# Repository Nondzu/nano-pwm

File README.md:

# nano-pwm
### PC fan controller based on arduino nano

_______________

##### This controller have 3 independent PWM channels with 25 kHz according to PC fan specification.

##### Serial port (9600bps) is use to communicate with  arduino nano. 

##### AT COMMAND:
* set PWM: <br />
`AT+PWM=$value` - set pwm value for all channels<br />
`AT+PWM=($channel, $value)` - set pwm $value for $channel<br />

* read RPM info: <br />
`AT?RPM` - get RPM values from all channels <br />

Each command must finish be new line character `\n`

example:<br />
`AT+PWM=50` - set all channel PWM to 50%<br />
`AT+PWM=(0,90)` - set channel 0 to 90% PWM. <br />
`AT+PWM=(2,50)` - set channel 2 to 50% PWM. <br />
`AT?RPM` - get rpm value from all channels<br />

-------
#### SCHEMATIC:
Schematic will be available soon. PWM and tachometer pins can by connecting directly to arduino. Additional items are not necessary (resistor or transistors).
here is connection info:<br /><br />
FAN PWM (OUTPUT):<br />
 PIN 9 - PWM output for channel 0<br />
 PIN 10 - PWM output for channel 1<br />
 PIN 3 - PWM output for channel 2<br />
<br />
FAN tachometer (INPUT):<br />
 PIN 4 - RPM CHANNEL 0<br />
 PIN 5 - RPM CHANNEL 1<br />
 PIN 6 - RPM CHANNEL 2<br />

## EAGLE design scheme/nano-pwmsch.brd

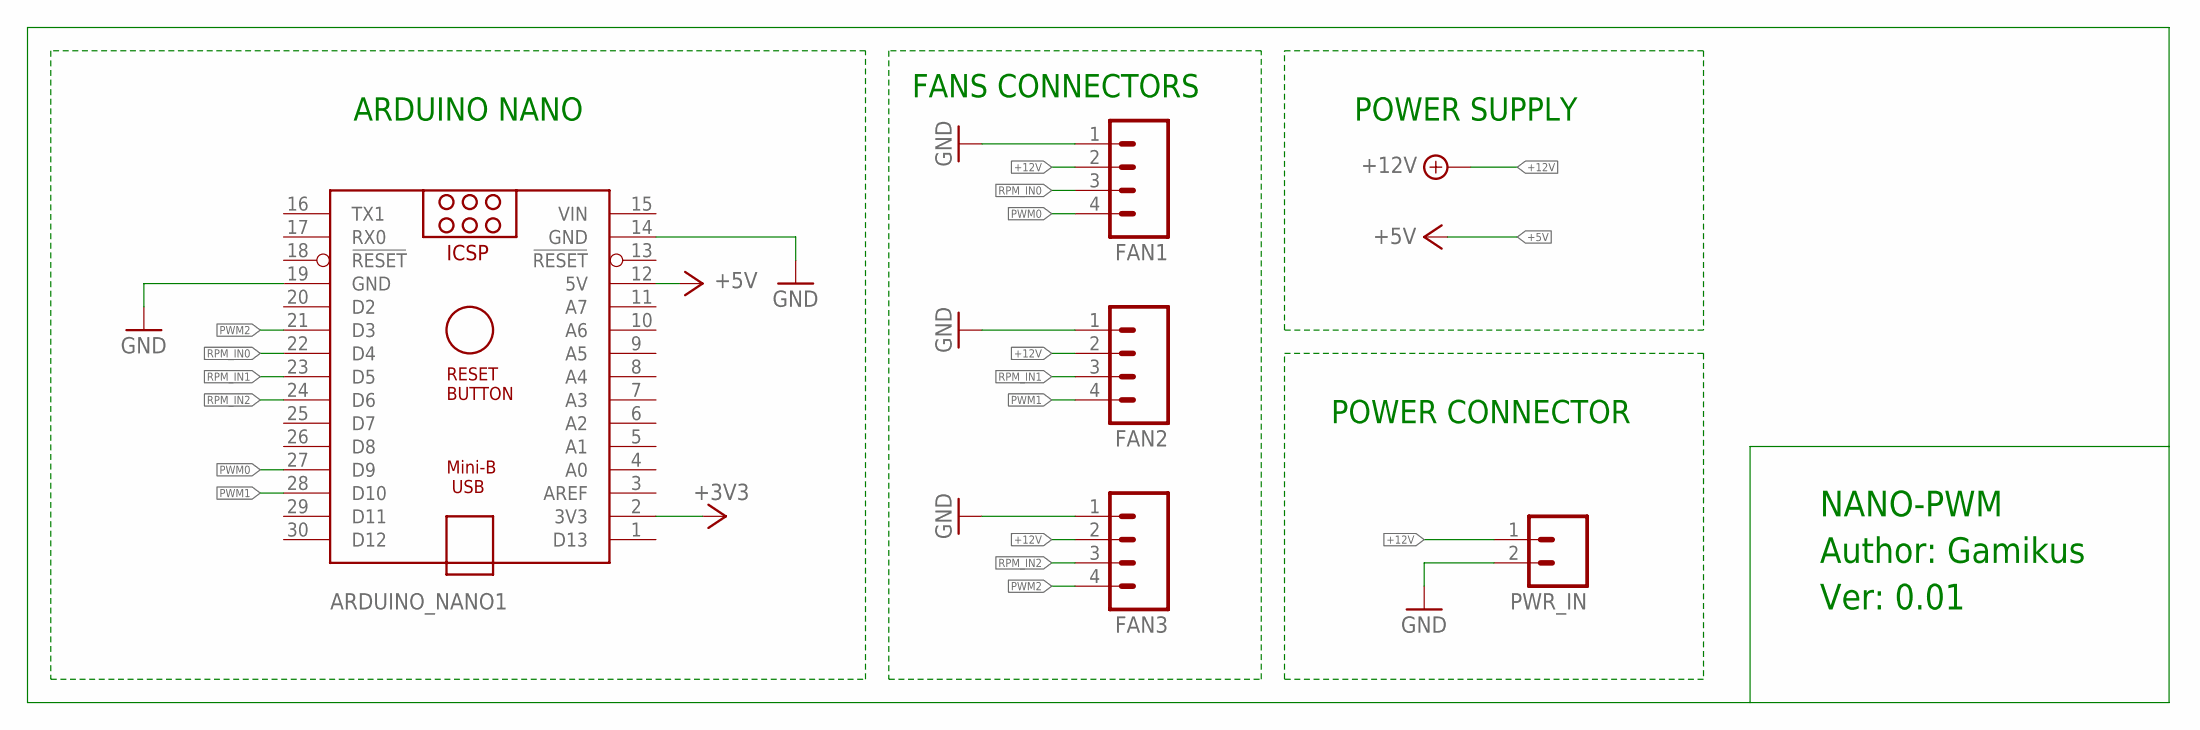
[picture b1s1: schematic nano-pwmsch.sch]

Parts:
ARDUINO_NANO1: ARDUINO_NANO
FAN1, FAN2, FAN3: M04; 04P
PWR_IN: M02; 02P

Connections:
+3V3: ARDUINO_NANO1.2 (3V3)
+5V: ARDUINO_NANO1.12 (5V)
+12V: FAN1.2, FAN2.2, FAN3.2, PWR_IN.1
GND: ARDUINO_NANO1.14 (GND), ARDUINO_NANO1.19 (GND), FAN1.1, FAN2.1, FAN3.1, PWR_IN.2
PWM0: ARDUINO_NANO1.27 (D9), FAN1.4
PWM1: ARDUINO_NANO1.28 (D10), FAN2.4
PWM2: ARDUINO_NANO1.21 (D3), FAN3.4
RPM_IN0: ARDUINO_NANO1.22 (D4), FAN1.3
RPM_IN1: ARDUINO_NANO1.23 (D5), FAN2.3
RPM_IN2: ARDUINO_NANO1.24 (D6), FAN3.3
VIN: ARDUINO_NANO1.15 (VIN)

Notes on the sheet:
Author: Gamikus
Ver: 0.01
NANO-PWM
ARDUINO NANO
FANS CONNECTORS
POWER SUPPLY
POWER CONNECTOR

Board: 2 copper layers, 5 parts (0 on the bottom side), 8 nets, no tracks yet.

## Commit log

2022-05-29 init
2022-05-29 create readne
2022-05-29 LICENSE
2022-05-29 1s timer events
2022-05-29 #5 pcint interrupt setup
2022-05-29 #4 rpm calculate
2022-05-29 #11: 3 channels PWM controll
2022-05-29 #2 at command
2022-06-13 move strings to FLASH memory
2022-06-26 electronic scheme (Eagle)
